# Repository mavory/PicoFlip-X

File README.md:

<div align="center">
  
# PicoFlip X 

PicoFlip X is a compact RP2040 development board with a built-in IMU for motion tracking, there's also a humidity and temperature sensor! It has several status LEDs, buttons,...
</div>

## Key Features

- DevBoard powered by RP2040 chip
- Humidity and temperature sensor built right on the PCB
- 2 LEDs for visual feedback (PWR and RST)
- IMU - MPU 6050 to monitor the board's current position, all built-in
- USB-C connectivity
- 2-layer PCB, so it's cost-effective to manufacture!
- Modified GPIO pin layout and added one extra +3V3
- Custom silkscreen with images and descriptions

## Why I made this project?

When I finished my last project, I was thinking again about what I could do... I thought I'd try something hard and test my nerves... 💀
So I was looking and came up with this project - DEVBOARD!!

## Schema and PCB
  <div align="center">
    
Here is the circuit diagram!

Next, here is the PCB that is created in KiCad:
<div align="center">

</div></div>

## The Design :)
  <div align="center">
    
Here is the top side of the PCB:

Also here is the bottom of the PCB!
<div align="center">

</div></div>

## JLCPCB Order
<div align="center">

</div>

## Bill of Materials

**Here is the complete BOM:**  

<details>
<summary>Click to expand!</summary>

| Top Designator | Comment | JLCPCB Part # | Product link | Lib Type | Qty | Source | Total Price ($) |
|---|---|---|---|---|---|---|---|
| C1,C10 | 1uF | C52923 | [Link](https://jlcpcb.com/partdetail/53938-CL05A105KA5NQNC/C52923) | Basic | 4 | 4 JLCPCB | 0,0132 |
| C2,C3,C4,C5,C6,C7,C8,C9,C11,C12,C17,C23 | 0.1uF | C1525 | [Link](https://jlcpcb.com/partdetail/1877-CL05B104KO5NNNC/C1525) | Basic | 32 | 32 JLCPCB | 0,0416 |
| C19,C21,C22,C24 | 100nF | ↑ | ↑ | ↑ | ↑ | ↑ | ↑ |
| C13,C14 | 10uF | C19702 | [Link](https://jlcpcb.com/partdetail/20411-CL10A106KP8NNNC/C19702) | Basic | 4 | 4 JLCPCB | 0,026 |
| C15,C16 | 33pF | C1562 | [Link](https://jlcpcb.com/partdetail/1914-0402CG330J500NT/C1562) | Basic | 4 | 4 JLCPCB | 0,0048 |
| C18,C25 | 10nF | C60133 | [Link](https://jlcpcb.com/partdetail/YAGEO-CC0402KRX7R9BB103/C60133) | Extended | 20 | 20 JLCPCB | 0,022 |
| C20 | 2.2uF | C12530 | [Link](https://jlcpcb.com/partdetail/13164-CL05A225MQ5NSNC/C12530) | Basic | 2 | 2 JLCPCB | 0,0052 |
| D3 | SK6812MINI | C7423117 | [Link](https://jlcpcb.com/partdetail/OPSCOOptoelectronics-SK6812MINIC/C7423117) | Extended | 5 | 5 JLCPCB | 0,428 |
| J1 | USB_C_Receptacle_USB2.0_14P | C165948 | [Link](https://jlcpcb.com/partdetail/Korean_HropartsElec-TYPE_C_31_M12/C165948) | Extended | 2 | 2 JLCPCB | 0,3624 |
| J2,J3 | Conn_01x20 | C50981 | [Link](https://jlcpcb.com/partdetail/51993-2_54_1_20P/C50981) | Extended | 4 | 4 JLCPCB | 0,4812 |
| J4 | Conn_01x03 | C49257 | [Link](https://jlcpcb.com/partdetail/50265-2_54_1_3P/C49257) | Extended | 4 | 4 JLCPCB | 0,0692 |
| PWR | POWER | C2286 | [Link](https://jlcpcb.com/partdetail/Hubei_KENTOElec-KT0603R/C2286) | Basic | 2 | 2 JLCPCB | 0,0128 |
| R1,R2 | 5.1K | C25905 | [Link](https://jlcpcb.com/partdetail/26648-0402WGF5101TCE/C25905) | Basic | 4 | 4 JLCPCB | 0,0032 |
| R3,R4 | 27 | C25100 | [Link](https://jlcpcb.com/partdetail/25843-0402WGF270JTCE/C25100) | Extended | 20 | 20 JLCPCB | 0,014 |
| R5,R6,R7 | 1K | C11702 | [Link](https://jlcpcb.com/partdetail/12256-0402WGF1001TCE/C11702) | Basic | 6 | 6 JLCPCB | 0,0042 |
| R8,R9 | 4.7K | C25900 | [Link](https://jlcpcb.com/partdetail/26643-0402WGF4701TCE/C25900) | Basic | 4 | 4 JLCPCB | 0,0032 |
| R10 | 10K | C25744 | [Link](https://jlcpcb.com/partdetail/26487-0402WGF1002TCE/C25744) | Basic | 2 | 2 JLCPCB | 0,0016 |
| R11,R12 | 680 | C25130 | [Link](https://jlcpcb.com/partdetail/25873-0402WGF6800TCE/C25130) | Extended | 20 | 20 JLCPCB | 0,016 |
| RST | RUN | C2288 | [Link](https://jlcpcb.com/partdetail/Hubei_KENTOElec-KT0603B/C2288) | Extended | 20 | 20 JLCPCB | 0,198 |
| SW1,SW2 | SW_Push | C720477 | [Link](https://jlcpcb.com/partdetail/XUNPU-TS_1088AR02016/C720477) | Basic | 4 | 4 JLCPCB | 0,1904 |
| U1 | RP2040 | C2040 | [Link](https://jlcpcb.com/partdetail/RaspberryPi-RP2040/C2040) | Extended | 2 | 2 JLCPCB | 1,9318 |
| U2 | MCP1700x-330xxTT | C39051 | [Link](https://jlcpcb.com/partdetail/MicrochipTech-MCP1700T_3302ETT/C39051) | Extended | 5 | 5 JLCPCB | 1,807 |
| U4 | SHT4x | C2848306 | [Link](https://jlcpcb.com/partdetail/Sensirion-SHT40_AD1BR3/C2848306) | Extended | 2 | 2 JLCPCB | 3,427 |
| U5 | W25Q16JVZPIQTR | C2843335 | [Link](https://jlcpcb.com/partdetail/WinbondElec-W25Q16JVUXIQ/C2843335) | Extended | 2 | 2 JLCPCB | 2,3964 |
| U6 | MPU-6050 | C24112 | [Link](https://jlcpcb.com/partdetail/TDKInvenSense-MPU6050/C24112) | Extended | 2 | 2 JLCPCB | 15,7754 |
| Y1 | 12MHz | C9002 | [Link](https://jlcpcb.com/partdetail/YXC_CrystalOscillators-X322512MSB4SI/C9002) | Basic | 2 | 2 JLCPCB | 0,1452 |
| PCBA (Parts + Assembly) |  |  |  |  |  |  | 65,32 |
| PCB (Black) |  |  |  |  |  |  | 4 |
| Shipping (GSDL) |  |  |  |  |  |  | 1,5 |
| TOTAL |  |  |  |  |  |  | 70,82 |

The bill of material is also available here: [BOM.csv](https://github.com/mavory/PicoFlip-X/blob/bba36edf56afa61a020f22f13432fc22c765aea1/BOM.csv)

</details>

<hr>
<div align="center">

Here is the link to the video: [YouTube](https://youtu.be/9DEOVKMEVFU)

<hr>

Made with ❤️ - by [@mavory](https://github.com/mavory) | Also thank you for providing the guide [@Kai Pereira](https://github.com/kaipereira)!

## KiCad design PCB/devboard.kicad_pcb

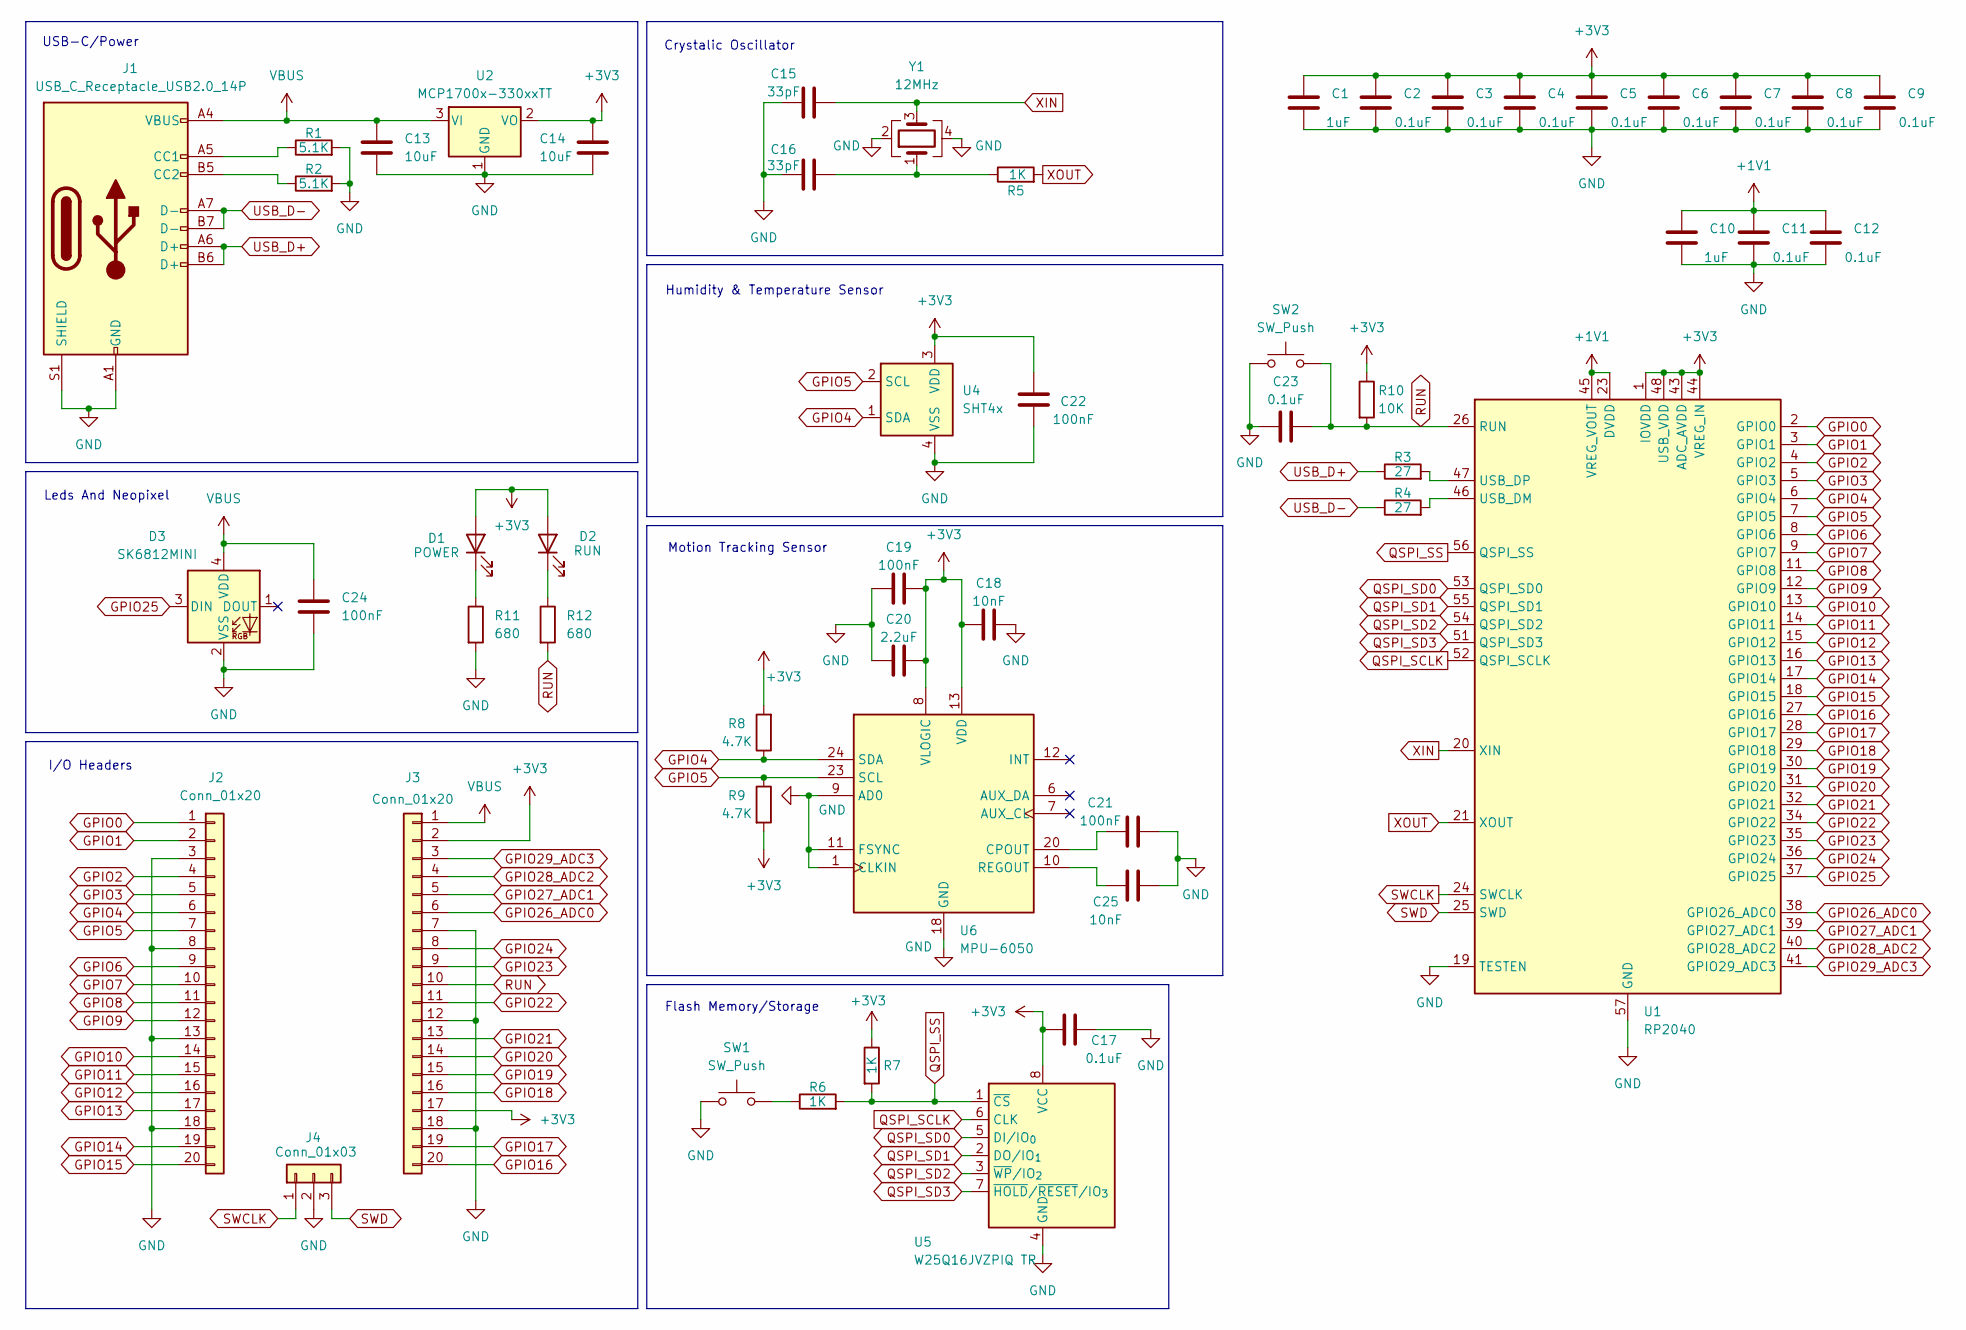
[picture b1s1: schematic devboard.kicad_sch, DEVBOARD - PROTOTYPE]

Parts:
C1, C10: 1uF; C_0402_1005Metric
C2, C3, C4, C5, C6, C7, C8, C9, C11, C12, C17, C23: 0.1uF; C_0402_1005Metric
C13, C14: 10uF; C_0603_1608Metric
C15, C16: 33pF; C_0402_1005Metric
C18, C25: 10nF; C_0402_1005Metric
C19, C21, C22, C24: 100nF; C_0402_1005Metric
C20: 2.2uF; C_0402_1005Metric
D1: POWER; LED_0603_1608Metric
D2: RUN; LED_0603_1608Metric
D3: SK6812MINI; LED_SK6812MINI_PLCC4_3.5x3.5mm_P1.75mm
J1: USB_C_Receptacle_USB2.0_14P; USB_C_Receptacle_HRO_TYPE-C-31-M-12
J2, J3: Conn_01x20; PinHeader_1x20_P2.54mm_Vertical
J4: Conn_01x03; PinHeader_1x03_P2.54mm_Vertical
R1, R2: 5.1K; R_0402_1005Metric
R3, R4: 27; R_0402_1005Metric
R5, R6, R7: 1K; R_0402_1005Metric
R8, R9: 4.7K; R_0402_1005Metric
R10: 10K; R_0402_1005Metric
R11, R12: 680; R_0402_1005Metric
SW1, SW2: SW_Push; SW_Push_SPST_NO_Alps_SKRK
U1: RP2040; QFN-56-1EP_7x7mm_P0.4mm_EP3.2x3.2mm
U2: MCP1700x-330xxTT; SOT-23
U4: SHT4x; Sensirion_DFN-4_1.5x1.5mm_P0.8mm_SHT4x_NoCentralPad
U5: W25Q16JVZPIQ TR; Winbond_USON-8-1EP_3x2mm_P0.5mm_EP0.2x1.6mm
U6: MPU-6050; InvenSense_QFN-24_4x4mm_P0.5mm
Y1: 12MHz; Crystal_SMD_3225-4Pin_3.2x2.5mm

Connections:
+1V1: C10.1, C11.1, C12.1, U1.23 (DVDD), U1.45 (VREG_VOUT), U1.50 (DVDD)
+3V3: C1.1, C2.1, C3.1, C4.1, C5.1, C6.1, C7.1, C8.1, C9.1, C14.1, C17.2, C18.1, C19.2, C20.2, C22.2, D1.2 (A), D2.2 (A), J3.2, J3.17, R7.1, R8.2, R9.2, R10.1, U1.1 (IOVDD), U1.10 (IOVDD), U1.22 (IOVDD), U1.33 (IOVDD), U1.42 (IOVDD), U1.43 (ADC_AVDD), U1.44 (VREG_IN), U1.48 (USB_VDD), U1.49 (IOVDD), U2.2 (VO), U4.3 (VDD), U5.8 (VCC), U6.8 (VLOGIC), U6.13 (VDD); also elsewhere on the board
GND: C1.2, C2.2, C3.2, C4.2, C5.2, C6.2, C7.2, C8.2, C9.2, C10.2, C11.2, C12.2, C13.2, C14.2, C15.1, C16.1, C17.1, C18.2, C19.1, C20.1, C21.2, C22.1, C23.1, C24.2, C25.2, D3.2 (VSS), J1.A1 (GND), J1.A12 (GND), J1.B1 (GND), J1.B12 (GND), J1.S1 (SHIELD), J2.3, J2.8, J2.13, J2.18, J3.7, J3.12, J3.18, J4.2, R1.2, R2.2, R11.2, SW1.1, SW2.1, U1.19 (TESTEN), U1.57 (GND), U2.1 (GND), U4.4 (VSS), U5.4 (GND), U6.1 (CLKIN), U6.9 (AD0), U6.11 (FSYNC), U6.18 (GND), Y1.2, Y1.4
GPIO0: J2.1, U1.2 (GPIO0)
GPIO1: J2.2, U1.3 (GPIO1)
GPIO2: J2.4, U1.4 (GPIO2)
GPIO3: J2.5, U1.5 (GPIO3)
GPIO4: J2.6, R8.1, U1.6 (GPIO4), U4.1 (SDA), U6.24 (SDA)
GPIO5: J2.7, R9.1, U1.7 (GPIO5), U4.2 (SCL), U6.23 (SCL)
GPIO6: J2.9, U1.8 (GPIO6)
GPIO7: J2.10, U1.9 (GPIO7)
GPIO8: J2.11, U1.11 (GPIO8)
GPIO9: J2.12, U1.12 (GPIO9)
GPIO10: J2.14, U1.13 (GPIO10)
GPIO11: J2.15, U1.14 (GPIO11)
GPIO12: J2.16, U1.15 (GPIO12)
GPIO13: J2.17, U1.16 (GPIO13)
GPIO14: J2.19, U1.17 (GPIO14)
GPIO15: J2.20, U1.18 (GPIO15)
GPIO16: J3.20, U1.27 (GPIO16)
GPIO17: J3.19, U1.28 (GPIO17)
GPIO18: J3.16, U1.29 (GPIO18)
GPIO19: J3.15, U1.30 (GPIO19)
GPIO20: J3.14, U1.31 (GPIO20)
GPIO21: J3.13, U1.32 (GPIO21)
GPIO22: J3.11, U1.34 (GPIO22)
GPIO23: J3.9, U1.35 (GPIO23)
GPIO24: J3.8, U1.36 (GPIO24)
GPIO25: D3.3 (DIN), U1.37 (GPIO25)
GPIO26_ADC0: J3.6, U1.38 (GPIO26_ADC0)
GPIO27_ADC1: J3.5, U1.39 (GPIO27_ADC1)
GPIO28_ADC2: J3.4, U1.40 (GPIO28_ADC2)
GPIO29_ADC3: J3.3, U1.41 (GPIO29_ADC3)
unnamed: C16.2, R5.1, Y1.1
unnamed 34: D1.1 (K), R11.1; also elsewhere on the board
unnamed 35: D2.1 (K), R12.1; also elsewhere on the board
unnamed: J1.A5 (CC1), R1.1
unnamed: J1.B5 (CC2), R2.1
unnamed: R6.1, SW1.2
unnamed: R4.2, U1.46 (USB_DM)
unnamed: R3.2, U1.47 (USB_DP)
unnamed: C21.1, U6.20 (CPOUT)
unnamed: C25.1, U6.10 (REGOUT)
QSPI_SCLK: U1.52 (QSPI_SCLK), U5.6 (CLK)
QSPI_SD0: U1.53 (QSPI_SD0), U5.5 (DI/IO_{0})
QSPI_SD1: U1.55 (QSPI_SD1), U5.2 (DO/IO_{1})
QSPI_SD2: U1.54 (QSPI_SD2), U5.3 (~WP/IO_{2})
QSPI_SD3: U1.51 (QSPI_SD3), U5.7 (~HOLD/~RESET/IO_{3})
QSPI_SS: R6.2, R7.2, U1.56 (QSPI_SS), U5.1 (~CS)
RUN: C23.2, J3.10, R10.2, R12.2, SW2.2, U1.26 (RUN)
SWCLK: J4.1, U1.24 (SWCLK)
SWD: J4.3, U1.25 (SWD)
USB_D+: J1.A6 (D+), J1.B6 (D+), R3.1
USB_D-: J1.A7 (D-), J1.B7 (D-), R4.1
VBUS: C13.1, C24.1, D3.4 (VDD), J1.A4 (VBUS), J1.A9 (VBUS), J1.B4 (VBUS), J1.B9 (VBUS), J3.1, U2.3 (VI)
XIN: C15.2, U1.20 (XIN), Y1.3
XOUT: R5.2, U1.21 (XOUT)

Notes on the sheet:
Leds And Neopixel
Flash Memory/Storage
Crystalic Oscillator
Motion Tracking Sensor
Humidity & Temperature Sensor
USB-C/Power
I/O Headers

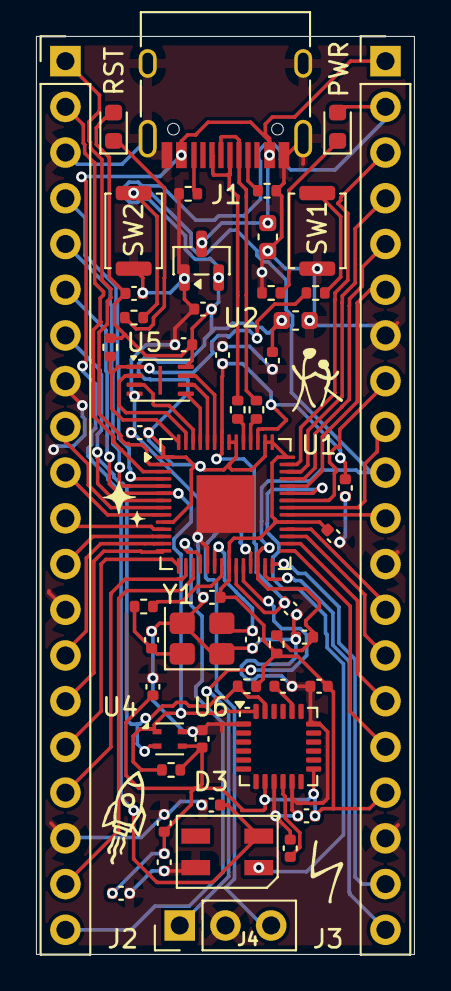
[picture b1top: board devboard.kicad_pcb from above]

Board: 2 copper layers, 21.0 x 51.0 mm, 52 parts (0 on the bottom side), 57 nets.

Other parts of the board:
PWR: POWER; LED_0603_1608Metric
RST: RUN; LED_0603_1608Metric

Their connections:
+3V3: PWR.2 (A), RST.2 (A); also elsewhere on the board
unnamed 34: PWR.1 (K); also elsewhere on the board
unnamed 35: RST.1 (K); also elsewhere on the board

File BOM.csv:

Designator,Comment,LCSC Part #,Typ (Lib Type),Price($)
"C1, C10",1uF,C52923,Basic,"0,0132"
"C2-C12, C17, C23",0.1uF / 100nF,C1525,Basic,"0,0416"
"C13, C14",10uF,C19702,Basic,"0,026"
"C15, C16",33pF,C1562,Basic,"0,0048"
"C18, C25",10nF,C60133,Extended,"0,022"
C20,2.2uF,C12530,Basic,"0,0052"
PWR,POWER LED,C2286,Basic,"0,0128"
RST,RUN LED,C2288,Extended,"0,198"
D3,SK6812MINI,C7423117,Extended,"0,428"
J1,USB-C 14P,C165948,Extended,"0,3624"
"J2, J3",Conn_01x20 (Piny),C50981,Extended,"0,4812"
J4,Conn_01x03 (Piny),C49257,Extended,"0,0692"
"R1, R2",5.1K,C25905,Basic,"0,0032"
"R3, R4",27,C25100,Extended,"0,014"
"R5, R6, R7",1K,C11702,Basic,"0,0042"
"R8, R9",4.7K,C25900,Basic,"0,0032"
R10,10K,C25744,Basic,"0,0016"
"R11, R12",680,C25130,Extended,"0,016"
"SW1, SW2",Tlačítka,C720477,Basic,"0,1904"
U1,RP2040,C2040,Extended,"1,9318"
U2,MCP1700T-3302E,C39051,Extended,"1,807"
U4,SHT40 (Senzor),C2848306,Extended,"3,427"
U5,W25Q16 (Flash),C2843335,Extended,"2,3964"
U6,MPU-6050 (Gyro),C24112,Extended,"15,7754"
Y1,12MHz Crystal,C9002,Basic,"0,1452"

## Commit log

2026-02-14 Create trash
2026-02-14 Diagram
2026-02-14 Printed Circuit Board
2026-02-14 .ZIP file
2026-02-14 Images and photos
2026-02-14 Bill of Materials
2026-02-14 Update BOM.csv with shipping details
    Added shipping information and ensured proper formatting.
2026-02-15 .ZIP files
2026-02-15 Update BOM.csv with new components and prices
2026-02-15 Update BOM.csv with new component entries
2026-02-15 JLCPCB
2026-02-15 Journal.md
2026-02-16 Renders
2026-02-16 Photos
2026-02-16 New prices
2026-02-16 Revise BOM format to include quantities
    Updated BOM to include quantity for each component and adjusted formatting.
2026-02-16 Revise BOM.csv for component details and pricing
    Updated component names and prices in BOM.
2026-02-16 Convert BOM.csv to standard CSV format
    Updated BOM.csv to use CSV format with headers and values.
2026-02-16 Fix BOM.csv formatting and restore header
2026-02-16 Update BOM.csv with new part details and links
2026-02-16 Update BOM.csv with new parts and pricing
2026-02-16 Update BOM.csv with new components and formatting
    The BOM.csv file was updated to include new entries and correct formatting issues.
2026-02-16 Revise README.md with project details and images
    Updated the README.md to enhance project description, features, and visuals.
2026-02-18 New files!
2026-02-18 New files added
2026-02-18 Create tatrgdgr
2026-02-18 New files
2026-02-18 PCB files
2026-02-26 PCBa
2026-03-28 Project photos
2026-03-28 DevBoard picture
2026-03-28 Change header image in README.md
    Updated the header image in the README file.
2026-03-28 Update journal entries and project details
2026-03-28 Add YouTube video link to README
    Added a link to a related YouTube video.
2026-03-28 Create Code
2026-03-28 Code
